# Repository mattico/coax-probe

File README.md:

# Coax Probes

**⚠️ NOTE:** I designed this as a learning experience. I never tested it very much, don't expect it to work well. In particular note [the limited common mode voltage range of the INA128](https://github.com/mattico/coax-probe/issues/1) which means this probe can't properly measure anything below 2V.

Simple, cheap, nearly disposable active electronic probes.

See the `lmh6642` branch for an even cheaper version with less bandwidth.

## License

Licensed under the terms of the *CERN Open Hardware Licence Version 2 - Weakly Reciprocal* see [the LICENSE file](LICENSE) for details.

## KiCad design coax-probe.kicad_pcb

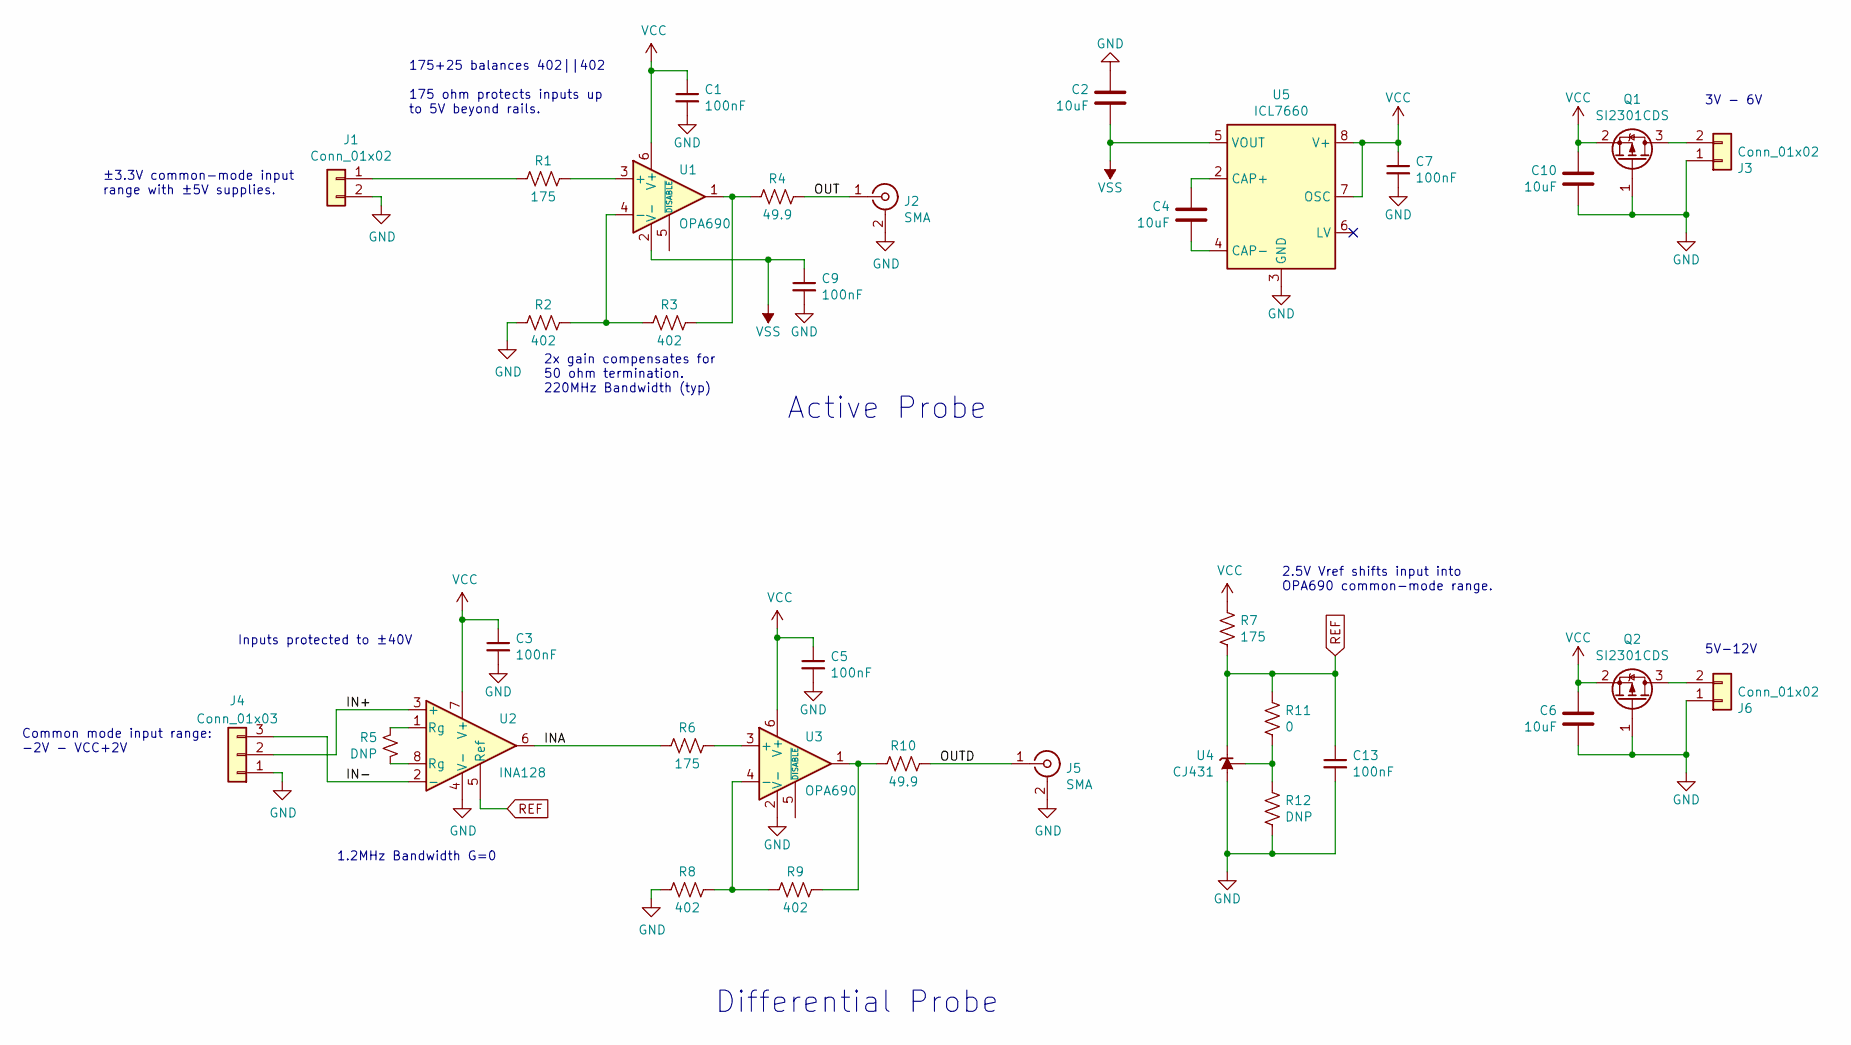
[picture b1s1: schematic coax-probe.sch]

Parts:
C1, C3, C5, C7, C9, C13: 100nF; C_0402_1005Metric; MPN CL05B104KO5NNNC; LCSC C1525
C2, C4, C6, C10: 10uF; C_0805_2012Metric; MPN CL21A106KAYNNNE; LCSC C15850
J1: Conn_01x02; PinHeader_1x02_P2.54mm_Vertical
J2, J5: SMA; SMA_Amphenol_132289_EdgeMount
J3, J6: Conn_01x02; PinHeader_1x02_P2.54mm_Horizontal
J4: Conn_01x03; PinHeader_1x03_P2.54mm_Vertical
Q1, Q2: SI2301CDS; SOT-23; LCSC C10487
R1, R6, R7: 175; R_0603_1608Metric; LCSC C22828
R2, R3, R8, R9: 402; R_0603_1608Metric; LCSC C23049
R4, R10: 49.9; R_0603_1608Metric; LCSC C23185
R5: DNP; R_0603_1608Metric_Pad0.98x0.95mm_HandSolder
R11: 0; R_0603_1608Metric; LCSC C21189
R12: DNP; R_0603_1608Metric
U1, U3: OPA690; TSOT-23-6; MPN OPA690IDBVT; LCSC C206074
U2: INA128; SOIC-8_3.9x4.9mm_P1.27mm; LCSC C22233
U4: CJ431; SOT-23; LCSC C3113
U5: ICL7660; SOIC-8_3.9x4.9mm_P1.27mm; LCSC C7881

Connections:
/IN+: J4.2, U2.3 (+)
/IN-: J4.3, U2.2 (-)
/INA: R6.2, U2.6
/OUT: J2.1 (In), R4.1
/OUTD: J5.1 (In), R10.1
GND: C1.2, C2.1, C3.2, C5.2, C6.1, C7.2, C9.2, C10.1, C13.2, J1.2, J2.2 (Ext), J3.1, J4.1, J5.2 (Ext), J6.1, Q1.1 (G), Q2.1 (G), R2.2, R8.2, R12.2, U2.4 (V-), U3.2 (V-), U4.3 (A), U5.3 (GND)
unnamed: C4.1, U5.2 (CAP+)
unnamed: C4.2, U5.4 (CAP-)
unnamed: J1.1, R1.2
unnamed: J3.2, Q1.3 (D)
unnamed: J6.2, Q2.3 (D)
unnamed: R1.1, U1.3 (+)
unnamed: R2.1, R3.2, U1.4 (-)
unnamed: R3.1, R4.2, U1.1
unnamed: R5.1, U2.8 (Rg)
unnamed: R5.2, U2.1 (Rg)
unnamed: R6.1, U3.3 (+)
unnamed: R8.1, R9.2, U3.4 (-)
unnamed: R9.1, R10.2, U3.1
unnamed: R11.2, R12.1, U4.1 (REF)
REF: C13.1, R7.2, R11.1, U2.5 (Ref), U4.2 (K)
VCC: C1.1, C3.1, C5.1, C6.2, C7.1, C10.2, Q1.2 (S), Q2.2 (S), R7.1, U1.6 (V+), U2.7 (V+), U3.6 (V+), U5.7 (OSC), U5.8 (V+)
VSS: C2.2, C9.1, U1.2 (V-), U5.5 (VOUT)

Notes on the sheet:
Differential Probe
5V-12V
Inputs protected to ±40V
Common mode input range: -2V - VCC+2V
1.2MHz Bandwidth G=0
Active Probe
2x gain compensates for 50 ohm termination. 220MHz Bandwidth (typ)
175+25 balances 402||402 175 ohm protects inputs up to 5V beyond rails.
3V - 6V
±3.3V common-mode input range with ±5V supplies.
2.5V Vref shifts input into OPA690 common-mode range.

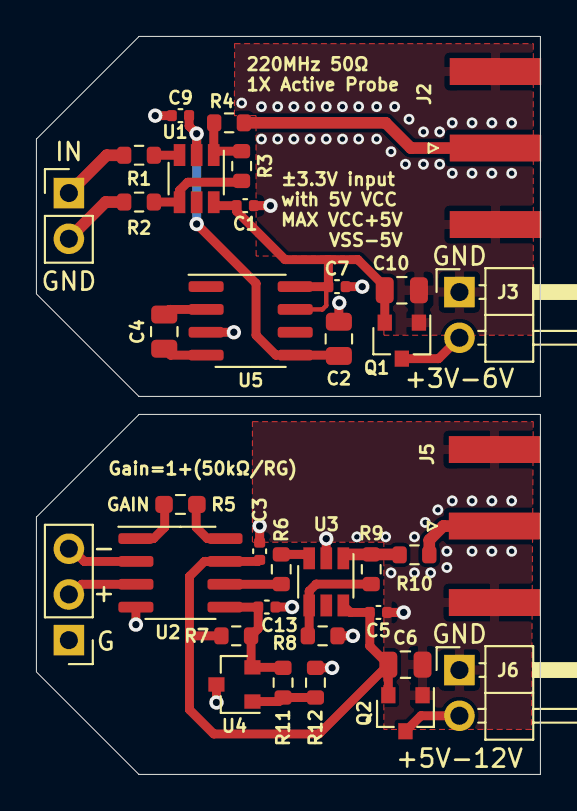
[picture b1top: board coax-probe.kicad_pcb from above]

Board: 2 copper layers, 28.0 x 41.0 mm, 35 parts (0 on the bottom side), 23 nets.

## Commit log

2021-03-31 use dual-supply for differential amp buffer
2021-03-31 Improvements, layout
2021-04-02 Add charge pump. Improve layout.
2021-04-02 Layout tweaks
2021-04-02 Fix 50-ohm trace width
2021-04-02 Use SMA connectors
2021-04-02 Tweak zones.
2021-04-03 Space out Vref more
2021-04-03 Widen PCBs for JLC assembly service
2021-04-03 Add fab outputs and part numbers
2021-04-03 Try out the LMH6642
2021-04-03 Add boilerplate
2021-04-03 Add lmh6642 branch to readme
2021-04-03 Add power reverse-polarity protection
